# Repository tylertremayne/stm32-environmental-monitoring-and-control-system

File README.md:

# STM32 Environmental Monitoring and Control System

#### An embedded environmental monitoring and fan control system built around the STM32F401RE.

## Planned Features
- Temperature sensing
- Ambient light sensing
- OLED display
- PWM-controlled DC fan
- UART telemetry
- Timer-driven sensor sampling
- Automatic and manual control modes

## Hardware
- STM32 Nucleo-F401RE

## Status
-- Project setup

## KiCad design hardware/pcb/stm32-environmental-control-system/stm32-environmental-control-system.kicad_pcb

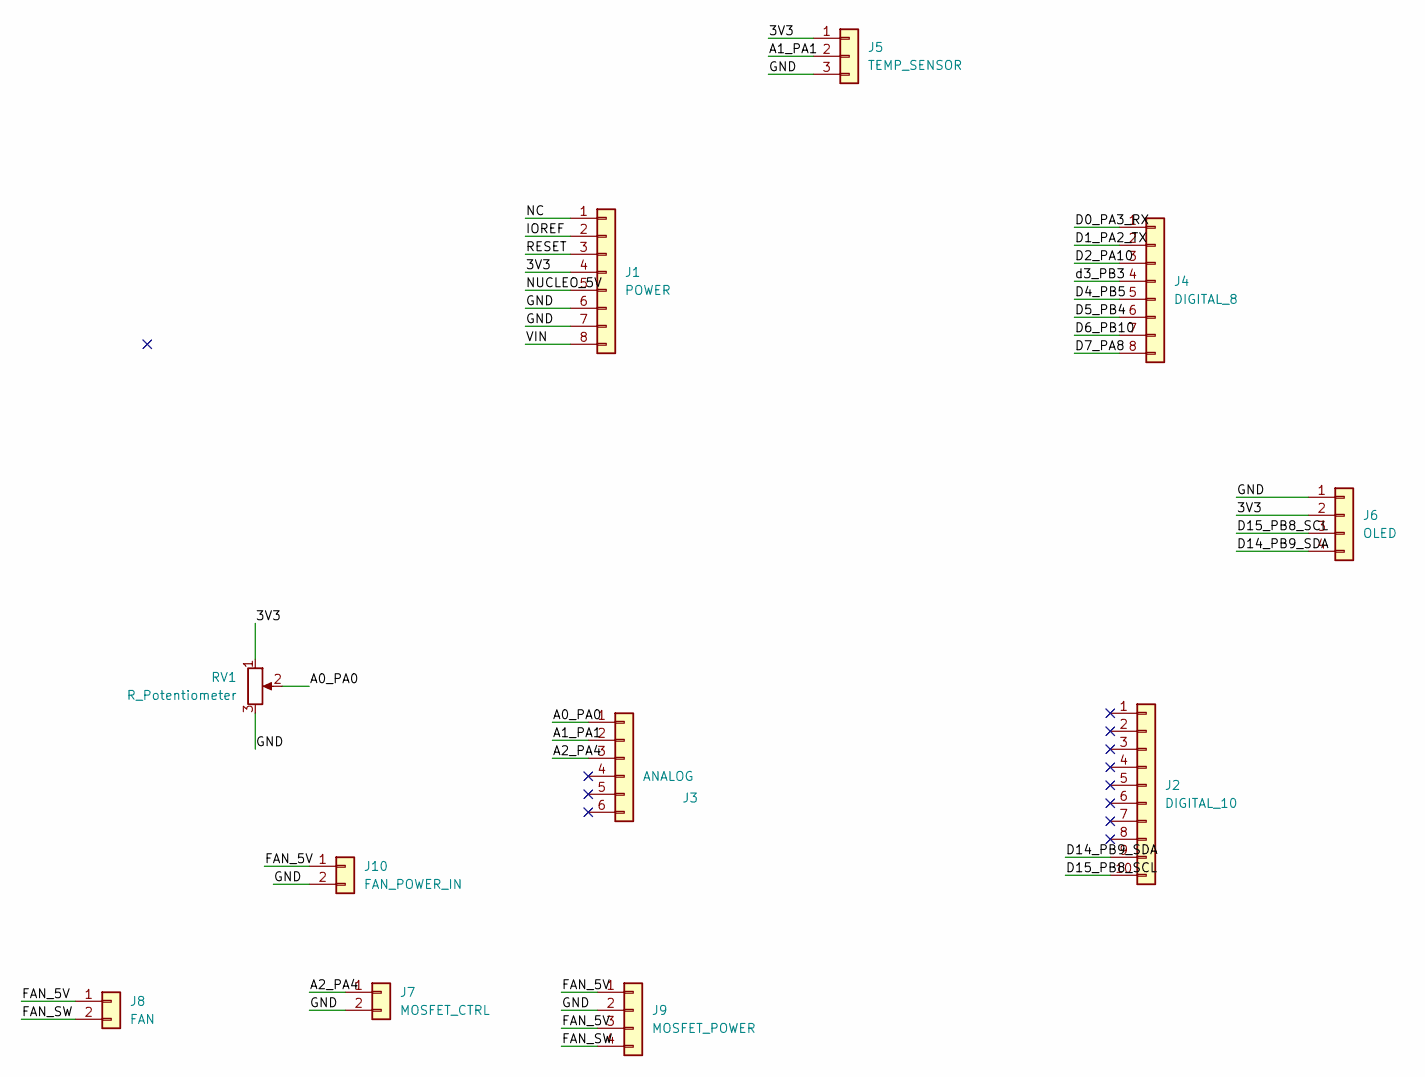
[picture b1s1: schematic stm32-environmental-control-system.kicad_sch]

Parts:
J1: POWER; PinHeader_1x08_P2.54mm_Vertical
J2: DIGITAL_10; PinHeader_1x10_P2.54mm_Vertical
J3: ANALOG; PinHeader_1x06_P2.54mm_Vertical
J4: DIGITAL_8; PinHeader_1x08_P2.54mm_Vertical
J5: TEMP_SENSOR; FanPinHeader_1x03_P2.54mm_Vertical
J6: OLED; FanPinHeader_1x04_P2.54mm_Vertical
J7: MOSFET_CTRL; PinHeader_1x02_P2.54mm_Vertical
J8: FAN; PinHeader_1x02_P2.54mm_Vertical
J9: MOSFET_POWER; FanPinHeader_1x04_P2.54mm_Vertical
J10: FAN_POWER_IN; PinHeader_1x02_P2.54mm_Vertical
RV1: R_Potentiometer; PinHeader_1x03_P2.54mm_Vertical

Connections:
/3V3: J1.4, J5.1, J6.2, RV1.1
/A0_PA0: J3.1, RV1.2
/A1_PA1: J3.2, J5.2
/A2_PA4: J3.3, J7.1
/D0_PA3_RX: J4.1
/D1_PA2_TX: J4.2
/D2_PA10: J4.3
/D4_PB5: J4.5
/D5_PB4: J4.6
/D6_PB10: J4.7
/D7_PA8: J4.8
/D14_PB9_SDA: J2.9, J6.4
/D15_PB8_SCL: J2.10, J6.3
/FAN_5V: J8.1, J9.1, J9.3, J10.1
/FAN_SW: J8.2, J9.4
/GND: J1.6, J1.7, J5.3, J6.1, J7.2, J9.2, J10.2, RV1.3
/IOREF: J1.2
/NC: J1.1
/NUCLEO_5V: J1.5
/RESET: J1.3
/VIN: J1.8
/d3_PB3: J4.4

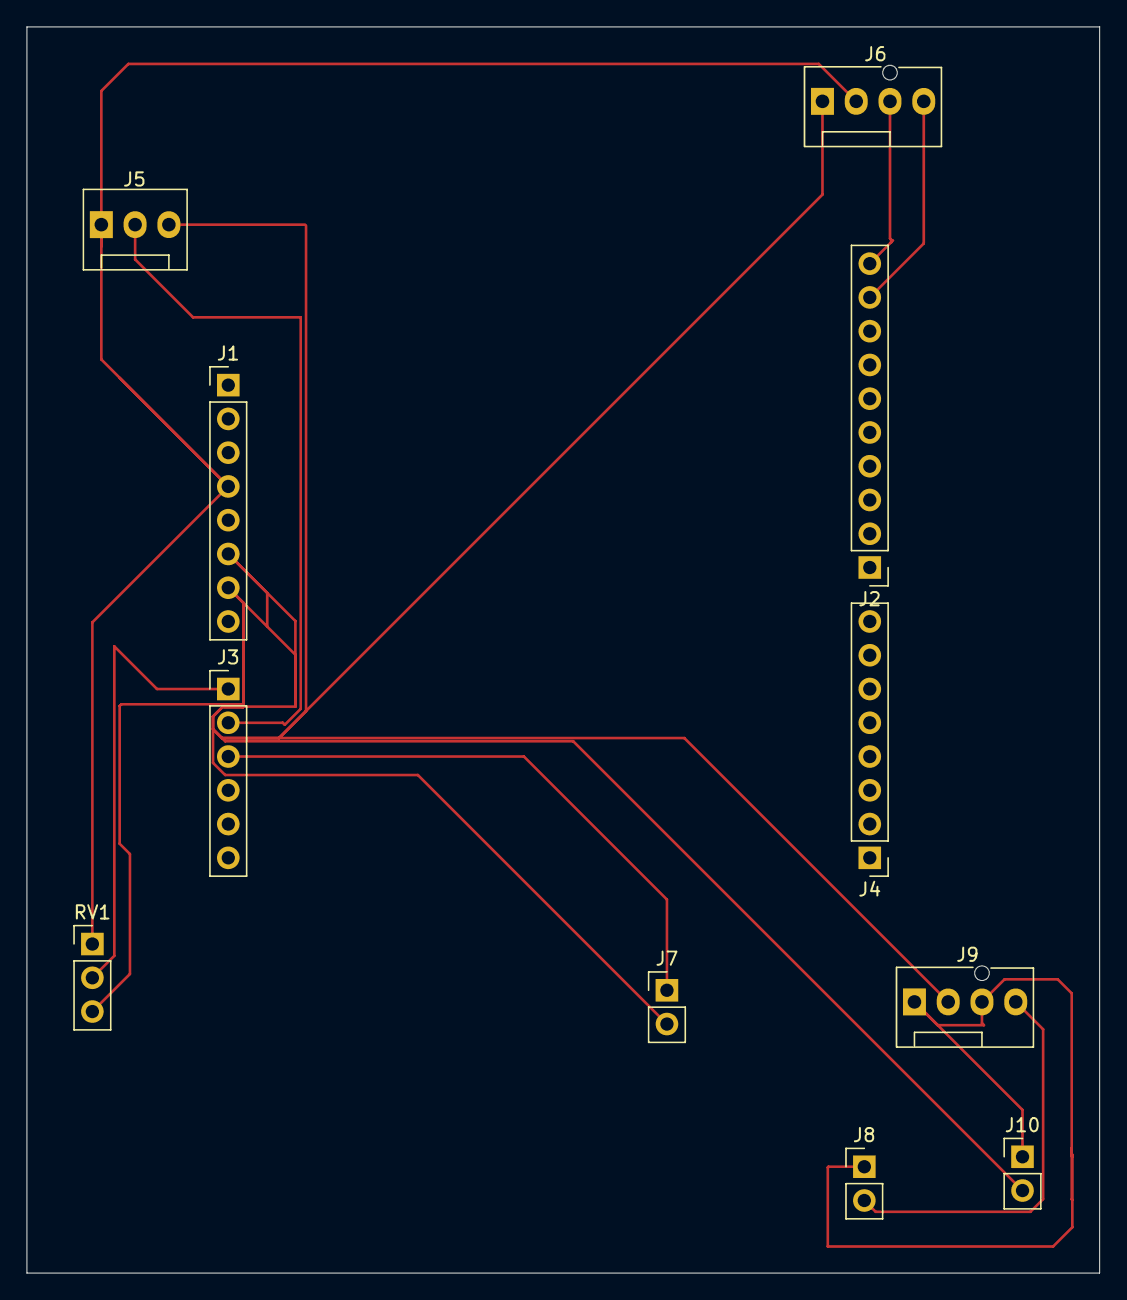
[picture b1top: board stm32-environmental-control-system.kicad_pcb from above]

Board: 2 copper layers, 80.7 x 93.8 mm, 11 parts (0 on the bottom side), 9 nets.
